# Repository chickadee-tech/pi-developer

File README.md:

# pi-developer
JTAG breakout for Raspberry Pi

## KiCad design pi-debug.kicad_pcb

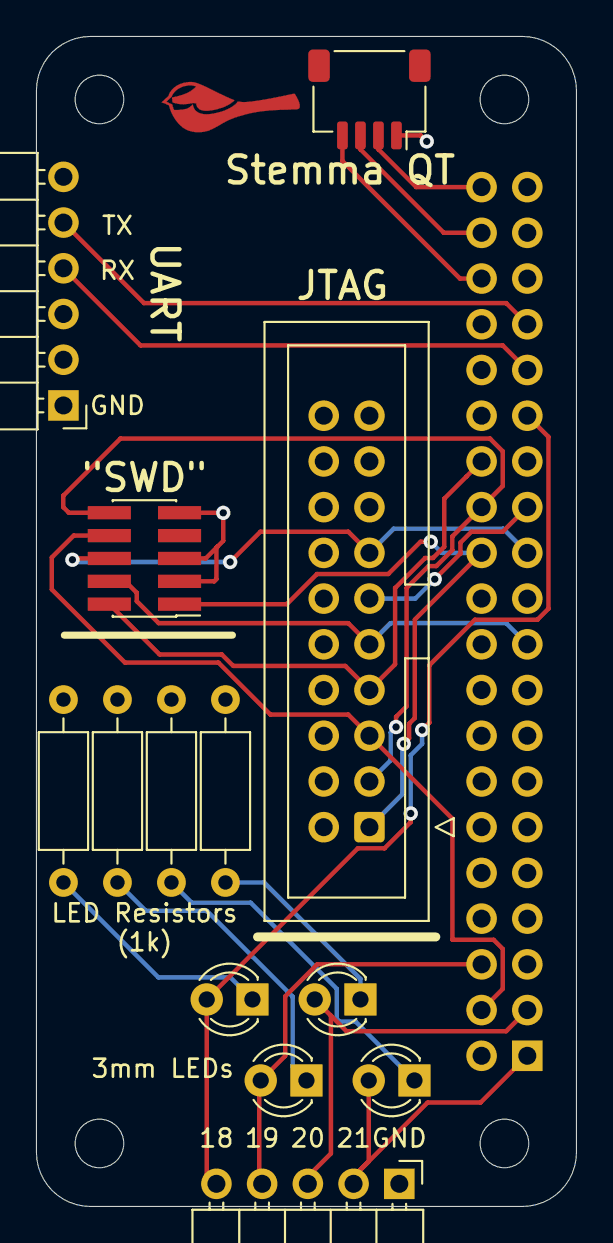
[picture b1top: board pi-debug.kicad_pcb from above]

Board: 2 copper layers, 30.0 x 65.0 mm, 14 parts (1 on the bottom side), 20 nets.

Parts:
D1, D2, D3, D4: LED_Small; LED_D3.0mm
J1: Conn_ARM_JTAG_SWD_20; IDC-Header_2x10_P2.54mm_Vertical
J2: Conn_01x06_Male; PinHeader_1x06_P2.54mm_Horizontal
J3: Conn_02x20_Odd_Even; PinSocket_2x20_P2.54mm_Vertical
J4: Conn_01x04_Male; JST_SH_SM04B-SRSS-TB_1x04-1MP_P1.00mm_Horizontal
J5: Conn_01x05_Male; PinHeader_1x05_P2.54mm_Horizontal
J6: Conn_ARM_JTAG_SWD_10; PinHeader_2x05_P1.27mm_Vertical_SMD
R1, R2, R3, R4: R_Small; R_Axial_DIN0207_L6.3mm_D2.5mm_P10.16mm_Horizontal

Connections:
+3V3: J1.1, J3.24, J3.40, J4.2, J6.1
/ARM_RTCK: J1.11, J3.25
/ARM_TCK: J1.9, J3.19, J6.4
/ARM_TDI: J1.5, J3.4, J6.8
/ARM_TDO: J1.13, J3.23, J6.6
/ARM_TMS: J1.7, J3.28, J6.2
/ARM_TRST: J1.3, J3.26, J6.10
/GPIO18: D1.2, J3.29, J5.5
/GPIO19: D2.2, J3.6, J5.4
/GPIO20: D3.2, J3.3, J5.3
/GPIO21: D4.2, J3.1, J5.2
/RX: J2.4, J3.31
/SCL: J3.36, J4.4
/SDA: J3.38, J4.3
/TX: J2.5, J3.33
GND: J1.4, J1.6, J1.8, J1.10, J1.12, J1.14, J1.16, J1.18, J1.20, J2.1, J3.2, J3.7, J3.11, J3.16, J3.21, J3.27, J3.32, J3.35, J4.1, J5.1, J6.3, J6.5, J6.9, R1.2, R2.2, R3.2, R4.2
unnamed: D1.1, R1.1
unnamed: D2.1, R2.1
unnamed: D3.1, R3.1
unnamed: D4.1, R4.1
